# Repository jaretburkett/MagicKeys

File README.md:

# Magic Keys

Magic Keys is an open source programmable keypad. The hardware is based on the Digispark/Arduino platform using the ATtiny85 microcontroller and a cheap button pad. A custom PCB was designed to attach to the button pad. The Eagle source files are in the hardware folder. We are in the process of designing our own button pad and they should be avaliable in the next few months.

####How It Works
The Attiny85 acts as a USB HID device and communicates button presses to the computer. There is a Node JS app (located in the app folder) that runs in the background. When a key is pressed, the NodeJS app will run the script associated with the button in the app/keys folder. (Key1 = 1.js etc). All you have to do is put the code you want to run on a button press in the appropriate button file and it will run on press. [RobotJS](https://github.com/octalmage/robotjs)  is automatically included in each one of those files, without needing to declare it. So, if you want a key to type Hello World. The only code needed in the key file is:
```
robot.typeString("Hello World");
```
Now, every time you push that button, it will type Hello World.

#### Required Hardware
The source files for the custom Magic Keys board located in the hardware folder is designed to solder onto 2 different keypad modules by RobotDyn. [4x4 module](http://robotdyn.com/catalog/buttons_control/button_keypad_4x4_module/) and [3x4 module](http://robotdyn.com/catalog/buttons_control/button_keypad_3x4_module/). We will be selling the addon board as well as a complete button pad shortly. For now, you can use a Digispark or roll your own pcb based on the design files provided.

####Plans
- Make a GUI app based on electron to make it easy to swap button functions on the fly
- Include a lot of example functions
- Make and sell complete keypads (open source)

####Install
######Hardware
>(Note: We are in the process of getting our own VID/PID and will compile complete firmware without the Digispark loader as soon as we have it. This process will change and become much easier.)

First you need Arduino with the Digispark board addon. [Instructions can be found here.](http://digistump.com/wiki/digispark/tutorials/connecting) You need to burn the micronucleus bootloader on the ATiny85 (v1.11) [located here.](https://github.com/micronucleus/micronucleus/tree/v1.11/firmware/releases). I highly recommend not disabling the reset fuse as the extra pin is not needed for this project.

Then, you need to load the code located in the arduino/MagicKeys folder onto the board.

######Software
You need to install [NodeJS](https://nodejs.org/en/). This was tested with v4.5.0 but should work with any version v0.8.0 and up. 
Navigate to the app directory and run:
```
npm install
```
When that is done, all you have to do is run:
```
node index.js
```
And the program should begin to run and look for your device. When a button is pressed, the javascript code in the keys directory for your button will run.

######Ubuntu/Linux
**Permissions**
Linux requires some permissions to access the usb devices directly. Create this file `/etc/udev/rules.d/49-magickeys.rules` and add the following line to it to grant the proper permissions.
`SUBSYSTEMS=="usb", ATTRS{idVendor}=="16c0", ATTRS{idProduct}=="05df", MODE:="0666"`
Then you can reload the rules with `sudo udevadm control --reload-rules`
You may need to reboot your system if the rules reload does not work.

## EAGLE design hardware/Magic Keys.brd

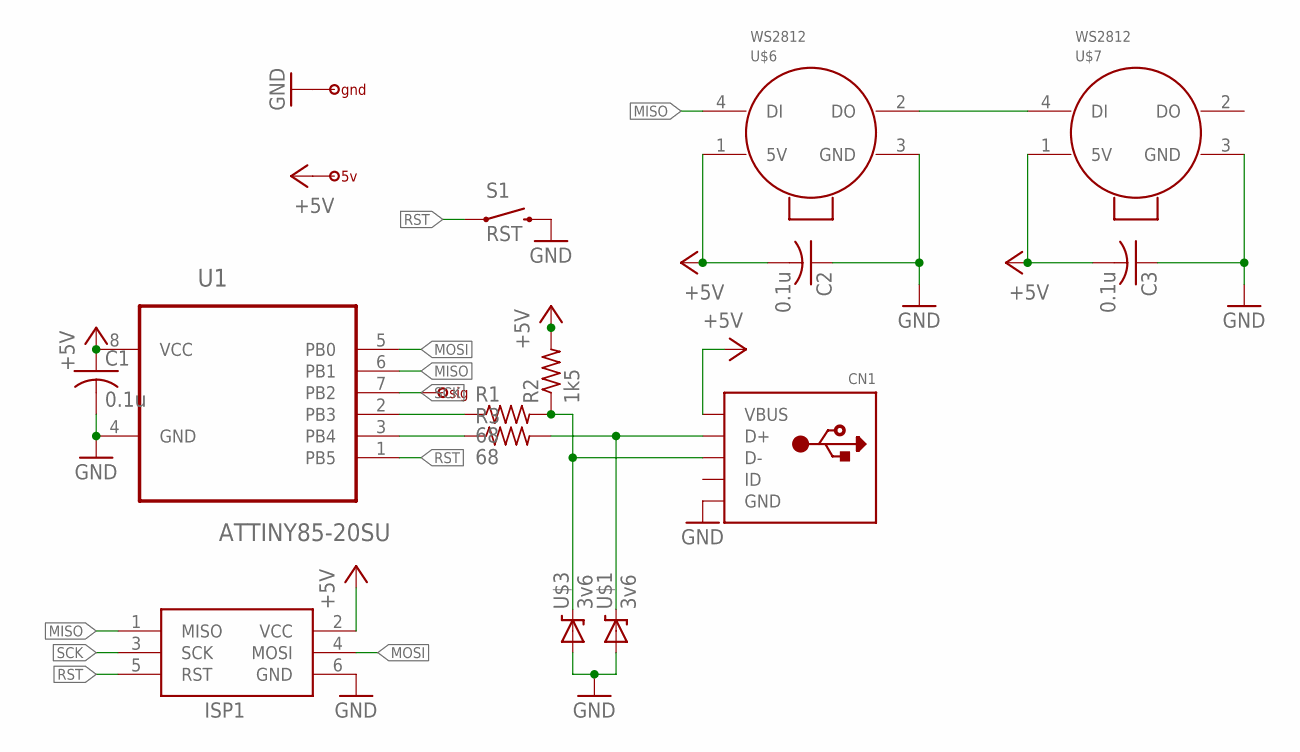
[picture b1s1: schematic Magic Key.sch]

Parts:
C1, C2, C3: 0.1u; C0603
CN1: USB_LEGS; MICRO_USB_LEGS
ISP1: AVRISP-6; AVRISP
R1, R3: 68; R0603
R2: 1k5; R0603
S1: RST; TACTILE-SWITCH-SMD
U1: ATTINY85-20SU; SOIC127P798X216-8N
U$1, U$3: 3v6; SOD-323
U$2: gnd; 1PIN
U$4: sig; 1PIN
U$5: 5v; 1PIN
U$6, U$7: WS2812

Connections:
+5V: C1.1, C2.2, C3.2, CN1.5 (VBUS), ISP1.2 (VCC), R2.2, U1.8 (VCC), U$5.P$1, U$6.1 (5V), U$7.1 (5V)
GND: C1.2, C2.1, C3.1, CN1.1 (GND), ISP1.6 (GND), S1.3 (2), U1.4 (GND), U$1.2 (A), U$2.P$1, U$3.2 (A), U$6.3 (GND), U$7.3 (GND)
MISO: ISP1.1 (MISO), U1.6 (PB1), U$6.4 (DI)
MOSI: ISP1.4 (MOSI), U1.5 (PB0)
unnamed: CN1.4 (D-), R1.2, R2.1, U$3.1 (C)
unnamed: CN1.3 (D+), R3.2, U$1.1 (C)
unnamed: R1.1, U1.2 (PB3)
unnamed: R3.1, U1.3 (PB4)
unnamed: U$6.2 (DO), U$7.4 (DI)
RST: ISP1.5 (RST), S1.1, U1.1 (PB5)
SCK: ISP1.3 (SCK), U1.7 (PB2), U$4.P$1

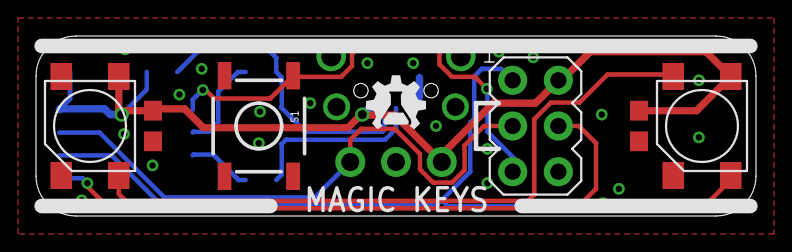
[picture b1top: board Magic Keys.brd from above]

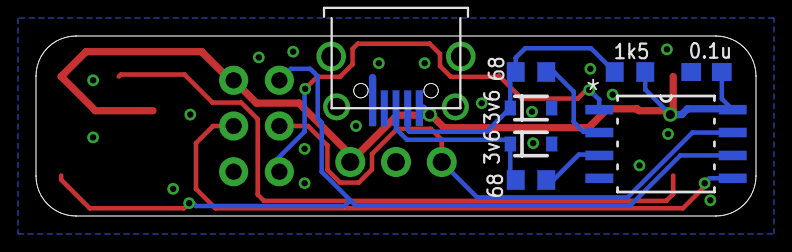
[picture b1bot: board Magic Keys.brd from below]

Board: 2 copper layers, 40.0 x 10.0 mm, 18 parts (8 on the bottom side), 11 nets.

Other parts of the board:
U$8: LOGO_3MM_SILK

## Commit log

2016-09-19 First
2016-09-19 Setup Node
2016-09-20 The base communication is working
2016-09-20 Did some cleanup
2016-09-21 Added Linux rules info
2016-09-21 Reorganized, added hardware files
2016-09-21 Created License file

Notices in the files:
parts and their libraries:
SparkFun-DiscreteSemi: Licensing: Creative Commons ShareAlike 4.0 International - https://creativecommons.org/licenses/by-sa/4.0
